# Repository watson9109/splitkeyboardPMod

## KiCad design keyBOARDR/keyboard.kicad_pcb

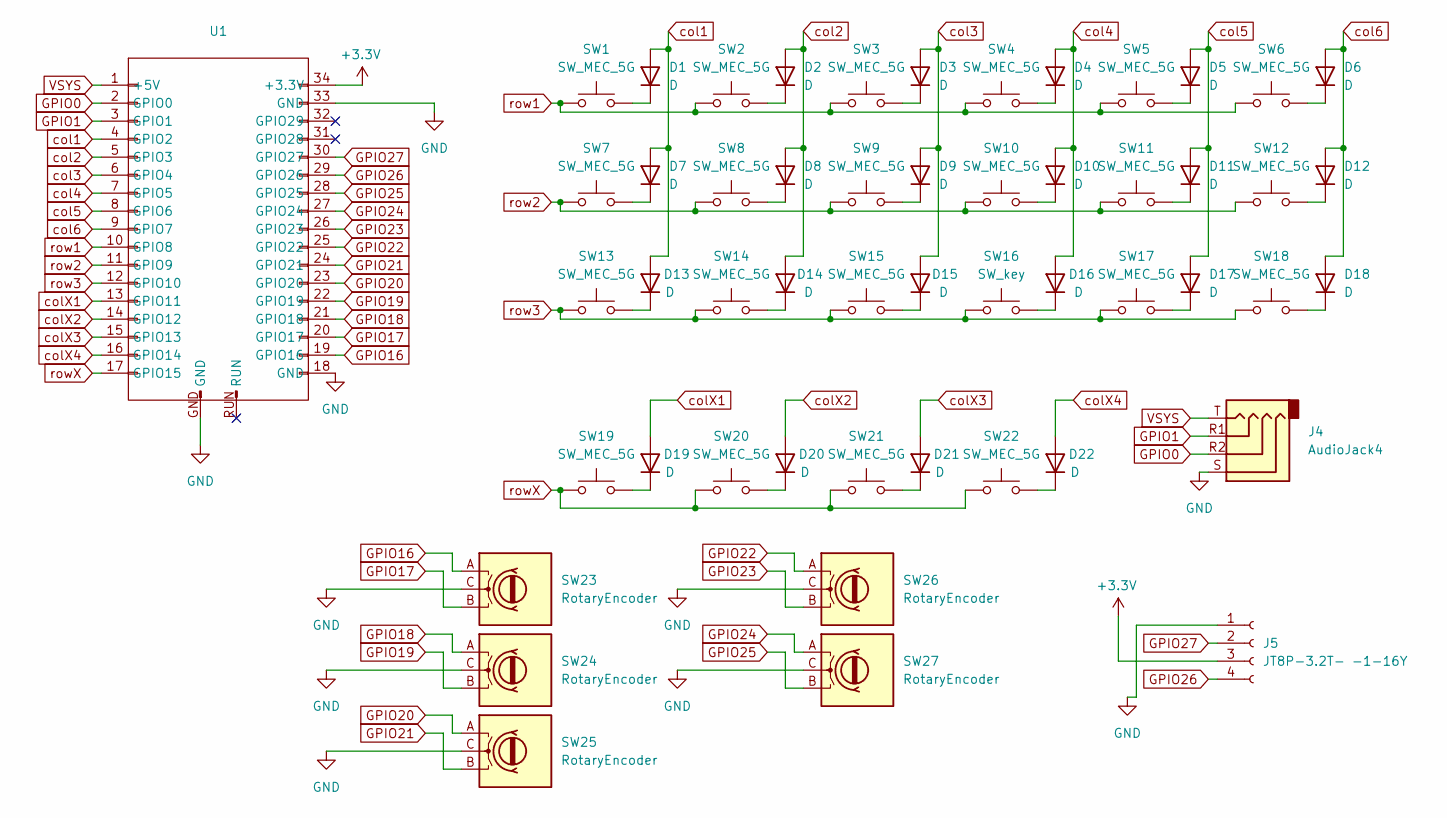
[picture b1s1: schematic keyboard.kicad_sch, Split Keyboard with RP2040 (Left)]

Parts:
D1, D2, D3, D4, D5, D6, D7, D8, D9, D10, D11, D12, D13, D14, D15, D16, D17, D18, D19, D20, D21, D22: D; D_DO-35_SOD27_P7.62mm_Horizontal
J4: AudioJack4; MJ-4PP-9
J5: JT8P-3.2T- -1-16Y
SW1, SW2, SW3, SW4, SW5, SW6, SW7, SW8, SW9, SW10, SW11, SW12, SW13, SW14, SW15, SW17, SW18, SW19, SW20, SW21, SW22: SW_MEC_5G; SW_Cherry_MX_1.00u_PCB
SW16: SW_key; SW_Cherry_MX_1.00u_PCB
SW23, SW24, SW25, SW26, SW27: RotaryEncoder; RotaryEncoder_Alps_EC12E_Vertical_H20mm_CircularMountingHol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
U1: AE-RP2040

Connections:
+3.3V: J5.3, U1.34 (+3.3V)
GND: J4.S, J5.1, SW23.C, SW24.C, SW25.C, SW26.C, SW27.C, U1.18 (GND), U1.33 (GND), U1.GND
GPIO0: J4.R2, U1.2 (GPIO0)
GPIO1: J4.R1, U1.3 (GPIO1)
GPIO16: SW23.A, U1.19 (GPIO16)
GPIO17: SW23.B, U1.20 (GPIO17)
GPIO18: SW24.A, U1.21 (GPIO18)
GPIO19: SW24.B, U1.22 (GPIO19)
GPIO20: SW25.A, U1.23 (GPIO20)
GPIO21: SW25.B, U1.24 (GPIO21)
GPIO22: SW26.A, U1.25 (GPIO22)
GPIO23: SW26.B, U1.26 (GPIO23)
GPIO24: SW27.A, U1.27 (GPIO24)
GPIO25: SW27.B, U1.28 (GPIO25)
GPIO26: J5.4, U1.29 (GPIO26)
GPIO27: J5.2, U1.30 (GPIO27)
unnamed: D1.1 (K), SW1.2 (B)
unnamed: D2.1 (K), SW2.2 (B)
unnamed: D3.1 (K), SW3.2 (B)
unnamed: D4.1 (K), SW4.2 (B)
unnamed: D5.1 (K), SW5.2 (B)
unnamed: D6.1 (K), SW6.2 (B)
unnamed: D7.1 (K), SW7.2 (B)
unnamed: D8.1 (K), SW8.2 (B)
unnamed: D9.1 (K), SW9.2 (B)
unnamed: D10.1 (K), SW10.2 (B)
unnamed: D11.1 (K), SW11.2 (B)
unnamed: D12.1 (K), SW12.2 (B)
unnamed: D13.1 (K), SW13.2 (B)
unnamed: D14.1 (K), SW14.2 (B)
unnamed: D15.1 (K), SW15.2 (B)
unnamed: D16.1 (K), SW16.2 (B)
unnamed: D17.1 (K), SW17.2 (B)
unnamed: D18.1 (K), SW18.2 (B)
unnamed: D19.1 (K), SW19.2 (B)
unnamed: D20.1 (K), SW20.2 (B)
unnamed: D21.1 (K), SW21.2 (B)
unnamed: D22.1 (K), SW22.2 (B)
VSYS: J4.T, U1.1 (+5V)
col1: D1.2 (A), D7.2 (A), D13.2 (A), U1.4 (GPIO2)
col2: D2.2 (A), D8.2 (A), D14.2 (A), U1.5 (GPIO3)
col3: D3.2 (A), D9.2 (A), D15.2 (A), U1.6 (GPIO4)
col4: D4.2 (A), D10.2 (A), D16.2 (A), U1.7 (GPIO5)
col5: D5.2 (A), D11.2 (A), D17.2 (A), U1.8 (GPIO6)
col6: D6.2 (A), D12.2 (A), D18.2 (A), U1.9 (GPIO7)
colX1: D19.2 (A), U1.13 (GPIO11)
colX2: D20.2 (A), U1.14 (GPIO12)
colX3: D21.2 (A), U1.15 (GPIO13)
colX4: D22.2 (A), U1.16 (GPIO14)
row1: SW1.1 (A), SW2.1 (A), SW3.1 (A), SW4.1 (A), SW5.1 (A), SW6.1 (A), U1.10 (GPIO8)
row2: SW7.1 (A), SW8.1 (A), SW9.1 (A), SW10.1 (A), SW11.1 (A), SW12.1 (A), U1.11 (GPIO9)
row3: SW13.1 (A), SW14.1 (A), SW15.1 (A), SW16.1 (A), SW17.1 (A), SW18.1 (A), U1.12 (GPIO10)
rowX: SW19.1 (A), SW20.1 (A), SW21.1 (A), SW22.1 (A), U1.17 (GPIO15)

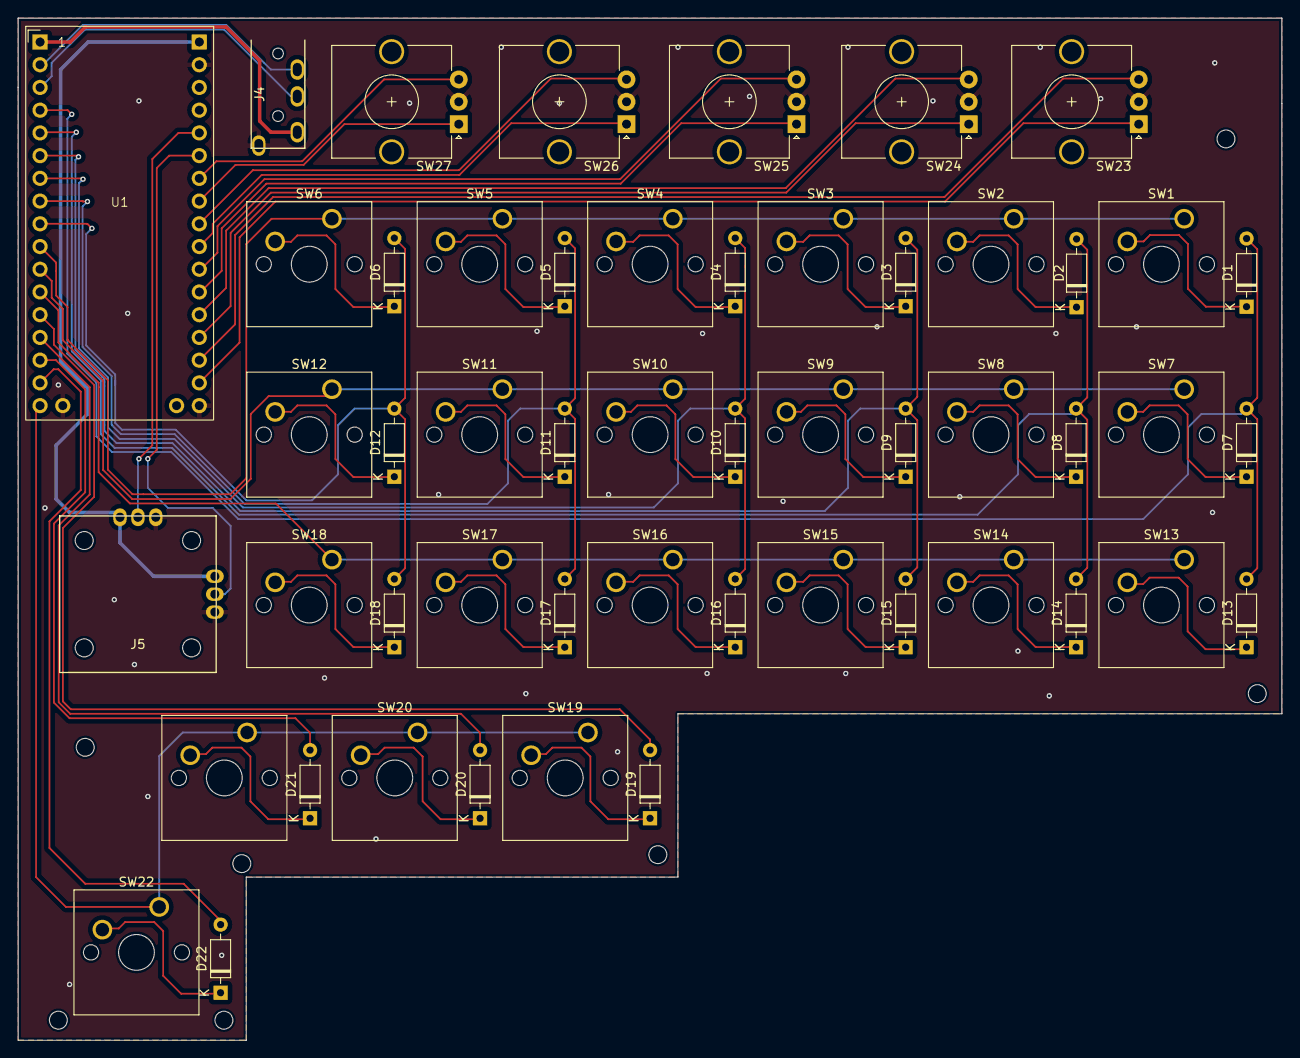
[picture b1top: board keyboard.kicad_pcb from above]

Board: 2 copper layers, 141.2 x 114.2 mm, 52 parts (0 on the bottom side), 53 nets.

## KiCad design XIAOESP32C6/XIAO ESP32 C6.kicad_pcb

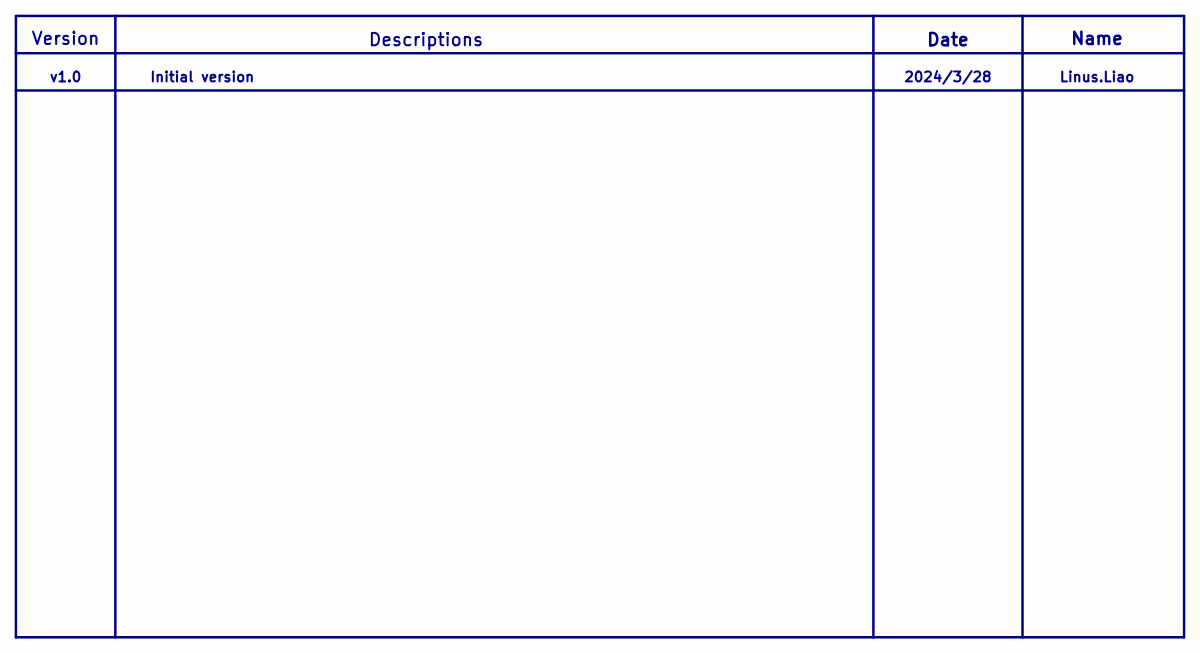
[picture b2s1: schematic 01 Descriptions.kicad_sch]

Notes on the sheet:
Date
Descriptions
Linus.Liao
2024/3/28
v1.0
Initial version
Name
Version

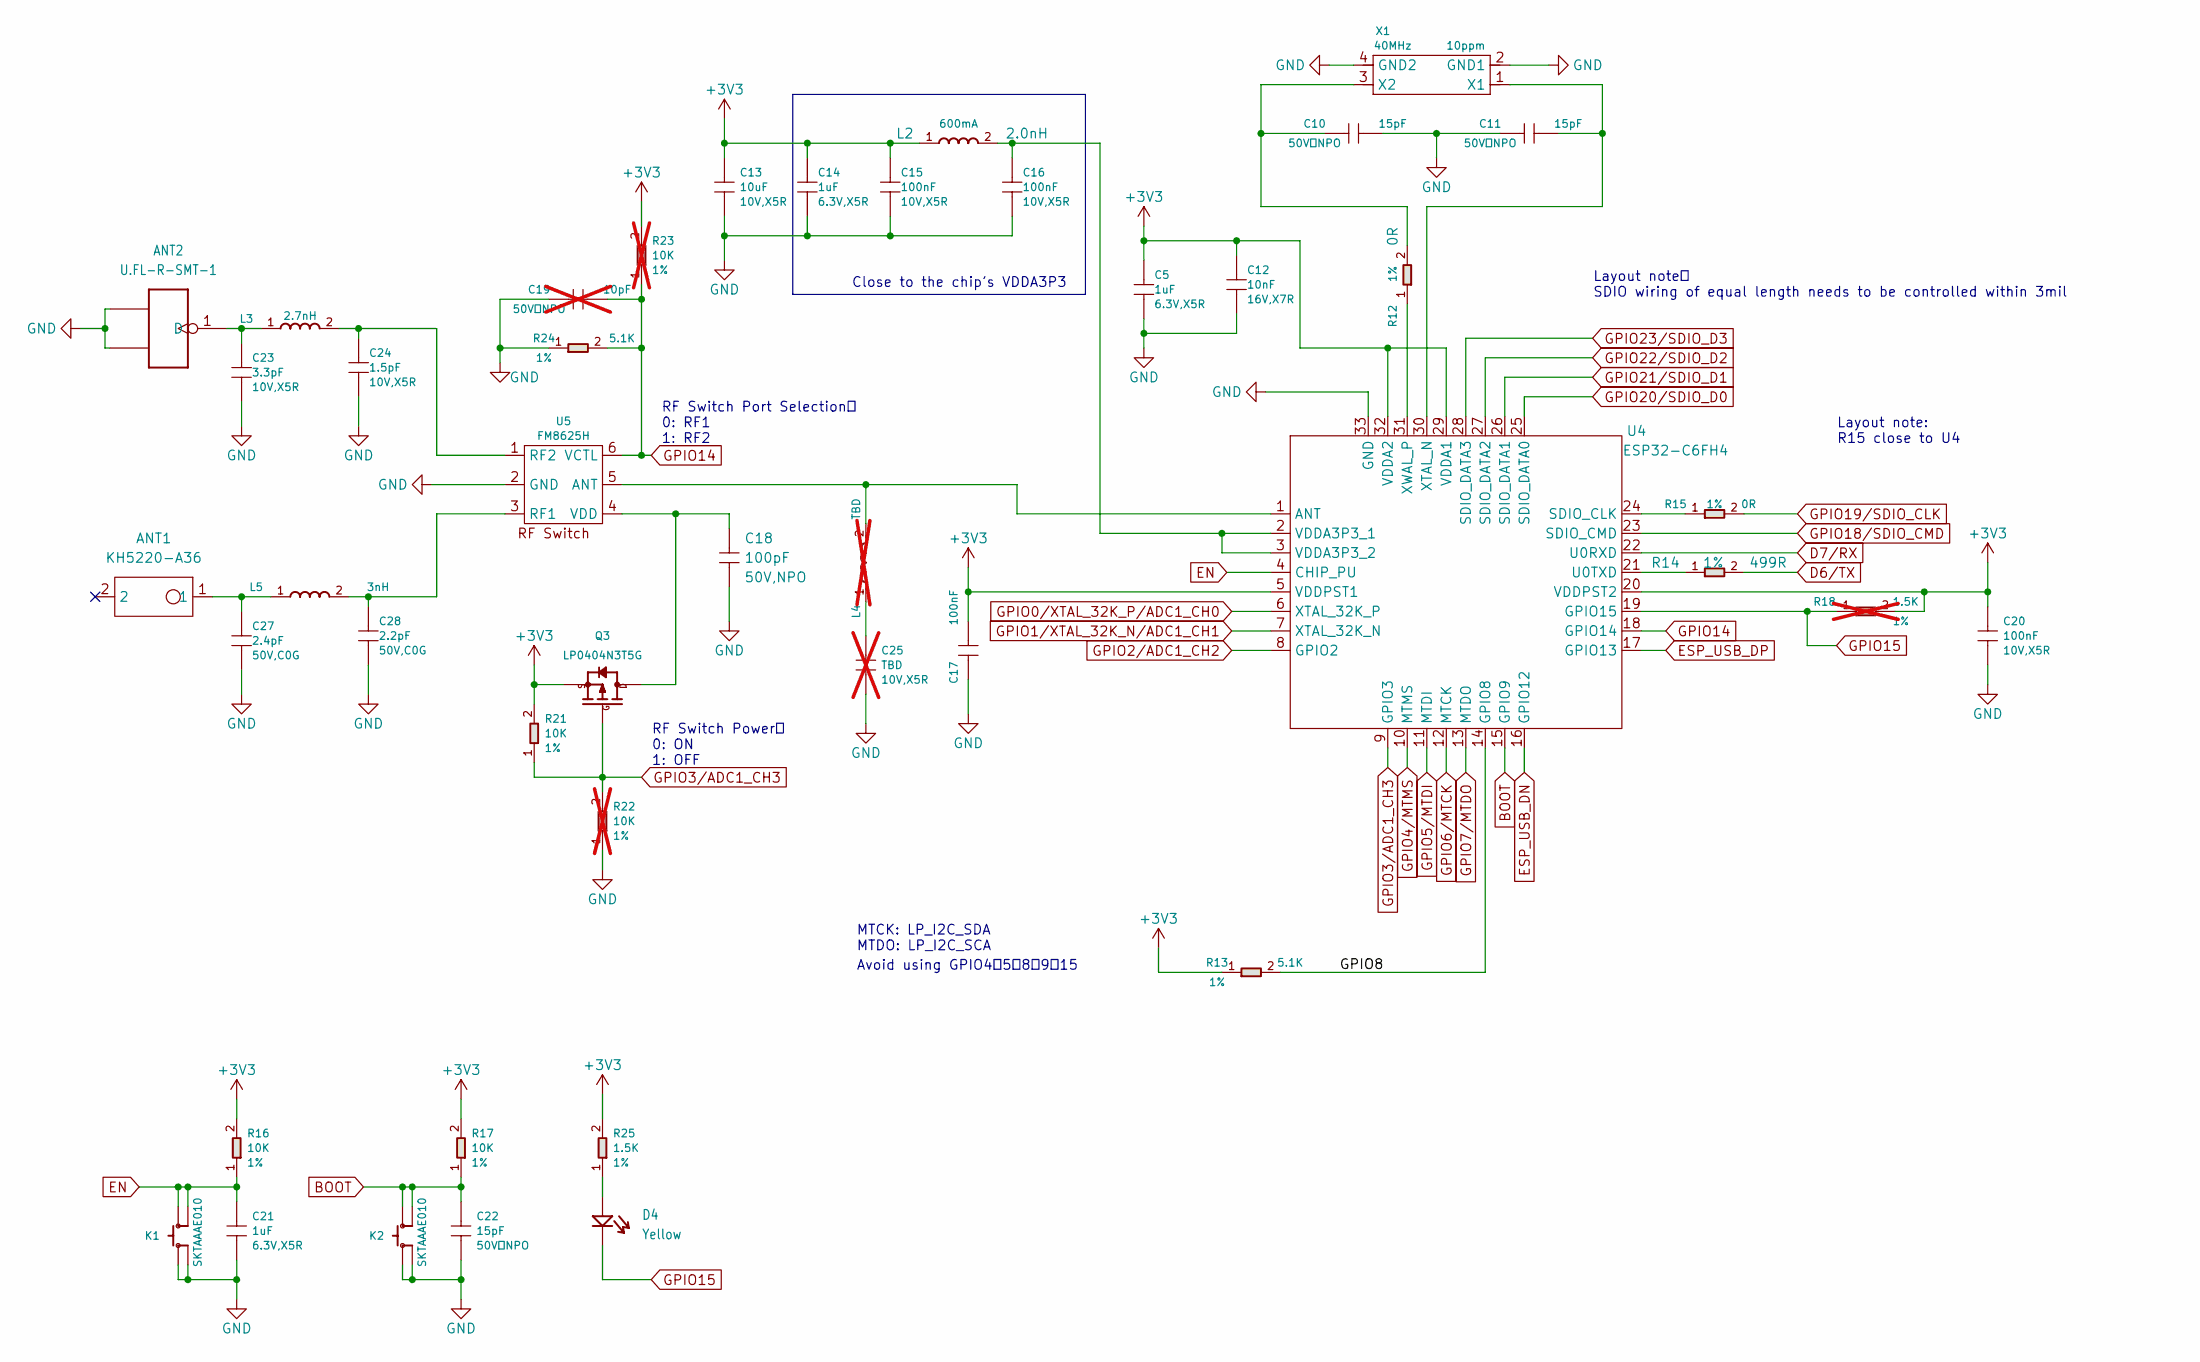
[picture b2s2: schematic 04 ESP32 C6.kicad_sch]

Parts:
ANT1: KH5220-A36; ANT2P-5.2x2x1.1MM; MPN KH5220-A36
ANT2: U.FL-R-SMT-1; U-FL3P-SMD-2.6X2.6X1.0MM; MPN U.FL-R-SMT-1
C5, C14, C21: 1uF; C0201; Voltage Rating 6.3V,X5R; MPN CC0201MRX5R5BB105
C10, C11, C22: 15pF; C0201; Voltage Rating 50V，NPO; MPN CC0201JRNPO9BN150
C12: 10nF; C0201; Voltage Rating 16V,X7R; MPN CC0201KRX7R7BB103
C13: 10uF; C0402; Voltage Rating 10V,X5R; MPN CC0402MRX5R6BB106
C15, C16, C17, C20: 100nF; C0201; Voltage Rating 10V,X5R; MPN CC0201KRX5R6BB104
C18: 100pF; C0201; Voltage Rating 50V,NPO; MPN CC0201JRNPO9BN101
C19: 10pF; C0201; Voltage Rating 50V，NPO; MPN CC0201JRNPO8BN100; not fitted
C23: 3.3pF; C0201; Voltage Rating 10V,X5R; MPN CQ0201BRNPO8BN3R3
C24: 1.5pF; C0201; Voltage Rating 10V,X5R; MPN CC0201BRNPO9BN1R5
C25: TBD; C0201; Voltage Rating 10V,X5R; Part Type Ceramic; not fitted
C27: 2.4pF; C0201; Voltage Rating 50V,C0G; MPN GRM0335C1H2R4BA01D
C28: 2.2pF; C0201; Voltage Rating 50V,C0G; MPN GRM0335C1H2R2BA01D
D4: Yellow; LED-0402; MPN 16-213/Y2C-AN2Q1B/3T
K1, K2: SKTAAAE010; SW4-SMD-2.8-2.6X1.6X0.53MM; MPN SKTAAAE010
L2: 2.0nH; L0201; Rating 600mA; MPN LQP03HQ2N0B02D
L3: 2.7nH; L0201; MPN LQP03TN2N7B02D
L4: TBD; L0201; Part Type L; not fitted
L5: 3nH; L0201; MPN LQP03TN3N0B02D
Q3: LP0404N3T5G; PMOS_1.0X0.6X0.35MM; MPN LP0404N3T5G
R12, R15: 0R; R0201; Power Rating 1%; MPN RC0201FR-070RL
R13, R24: 5.1K; R0201; Power Rating 1%; MPN RC0201FR-075K1L
R14: 499R; R0201; Power Rating 1%; MPN RC0201FR-07499RL
R16, R17, R21: 10K; R0201; Power Rating 1%; MPN RC0201FR-0710KL
R18: 1.5K; R0201; Power Rating 1%; MPN RC0201FR-071K5L; not fitted
R22, R23: 10K; R0201; Power Rating 1%; MPN RC0201FR-0710KL; not fitted
R25: 1.5K; R0201; Power Rating 1%; MPN RC0201FR-071K5L
U4: ESP32-C6FH4; QFN32-0.5-5X5MM; MPN ESP32-C6FH4
U5: FM8625H; DFN6-0.4-1.1X0.7X0.45MM; MPN FM8625H
X1: 40MHz; X4-SMD-1.6X1.2MM; Rating 10ppm; MPN CJ17-400001010B20

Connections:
+3V3: C5.1, C12.1, C13.1, C14.1, C15.1, C17.1, C20.1, L2.1, Q3.2 (S), R13.1, R16.2, R17.2, R18.2, R21.2, R23.2, R25.2, U4.5 (VDDPST1), U4.20 (VDDPST2), U4.29 (VDDA1), U4.32 (VDDA2); also elsewhere on the board
/04 ESP32 C6/GPIO8: R13.2, U4.14 (GPIO8)
BOOT: C22.1, K2.3 (B0), K2.4 (B1), R17.1, U4.15 (GPIO9); also elsewhere on the board
D6/TX: R14.2; also elsewhere on the board
D7/RX: U4.22 (U0RXD); also elsewhere on the board
EN: C21.1, K1.3 (B0), K1.4 (B1), R16.1, U4.4 (CHIP_PU); also elsewhere on the board
ESP_USB_DN: U4.16 (GPIO12); also elsewhere on the board
ESP_USB_DP: U4.17 (GPIO13); also elsewhere on the board
GND: ANT2.2 (GND1), ANT2.3 (GND2), C5.2, C10.2, C11.1, C12.2, C13.2, C14.2, C15.2, C16.2, C17.2, C18.2, C19.1, C20.2, C21.2, C22.2, C23.2, C24.2, C25.2, C27.2, C28.2, K1.1 (A0), K1.2 (A1), K2.1 (A0), K2.2 (A1), R22.1, R24.1, U4.33 (GND), U5.2 (GND), X1.2 (GND1), X1.4 (GND2); also elsewhere on the board
GPIO0/XTAL_32K_P/ADC1_CH0: U4.6 (XTAL_32K_P); also elsewhere on the board
GPIO1/XTAL_32K_N/ADC1_CH1: U4.7 (XTAL_32K_N); also elsewhere on the board
GPIO2/ADC1_CH2: U4.8 (GPIO2); also elsewhere on the board
GPIO3/ADC1_CH3: Q3.1 (G), R21.1, R22.2, U4.9 (GPIO3)
GPIO4/MTMS: U4.10 (MTMS); also elsewhere on the board
GPIO5/MTDI: U4.11 (MTDI); also elsewhere on the board
GPIO6/MTCK: U4.12 (MTCK); also elsewhere on the board
GPIO7/MTDO: U4.13 (MTDO); also elsewhere on the board
GPIO14: C19.2, R23.1, R24.2, U4.18 (GPIO14), U5.6 (VCTL)
GPIO15: D4.2 (-), R18.1, U4.19 (GPIO15)
GPIO18/SDIO_CMD: U4.23 (SDIO_CMD); also elsewhere on the board
GPIO19/SDIO_CLK: R15.2; also elsewhere on the board
GPIO20/SDIO_D0: U4.25 (SDIO_DATA0); also elsewhere on the board
GPIO21/SDIO_D1: U4.26 (SDIO_DATA1); also elsewhere on the board
GPIO22/SDIO_D2: U4.27 (SDIO_DATA2); also elsewhere on the board
GPIO23/SDIO_D3: U4.28 (SDIO_DATA3); also elsewhere on the board
unnamed: ANT1.1, C27.1, L5.1
unnamed: ANT2.1 (D), C23.1, L3.1
unnamed: C25.1, L4.1
unnamed: D4.1 (+), R25.1
unnamed: C18.1, Q3.3 (D), U5.4 (VDD)
unnamed: L4.2, U4.1 (ANT), U5.5 (ANT)
unnamed: R15.1, U4.24 (SDIO_CLK)
unnamed: R14.1, U4.21 (U0TXD)
unnamed: C16.1, L2.2, U4.2 (VDDA3P3_1), U4.3 (VDDA3P3_2)
unnamed: C11.2, U4.30 (XTAL_N), X1.1 (X1)
unnamed: R12.1, U4.31 (XWAL_P)
unnamed: C28.1, L5.2, U5.3 (RF1)
unnamed: C24.1, L3.2, U5.1 (RF2)
unnamed: C10.1, R12.2, X1.3 (X2)

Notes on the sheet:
Avoid using GPIO4、5、8、9、15
RF Switch Power： 0: ON 1: OFF
Layout note: R15 close to U4
Close to the chip's VDDA3P3
Layout note： SDIO wiring of equal length needs to be controlled within 3mil
RF Switch Port Selection： 0: RF1 1: RF2
MTCK: LP_I2C_SDA MTDO: LP_I2C_SCA

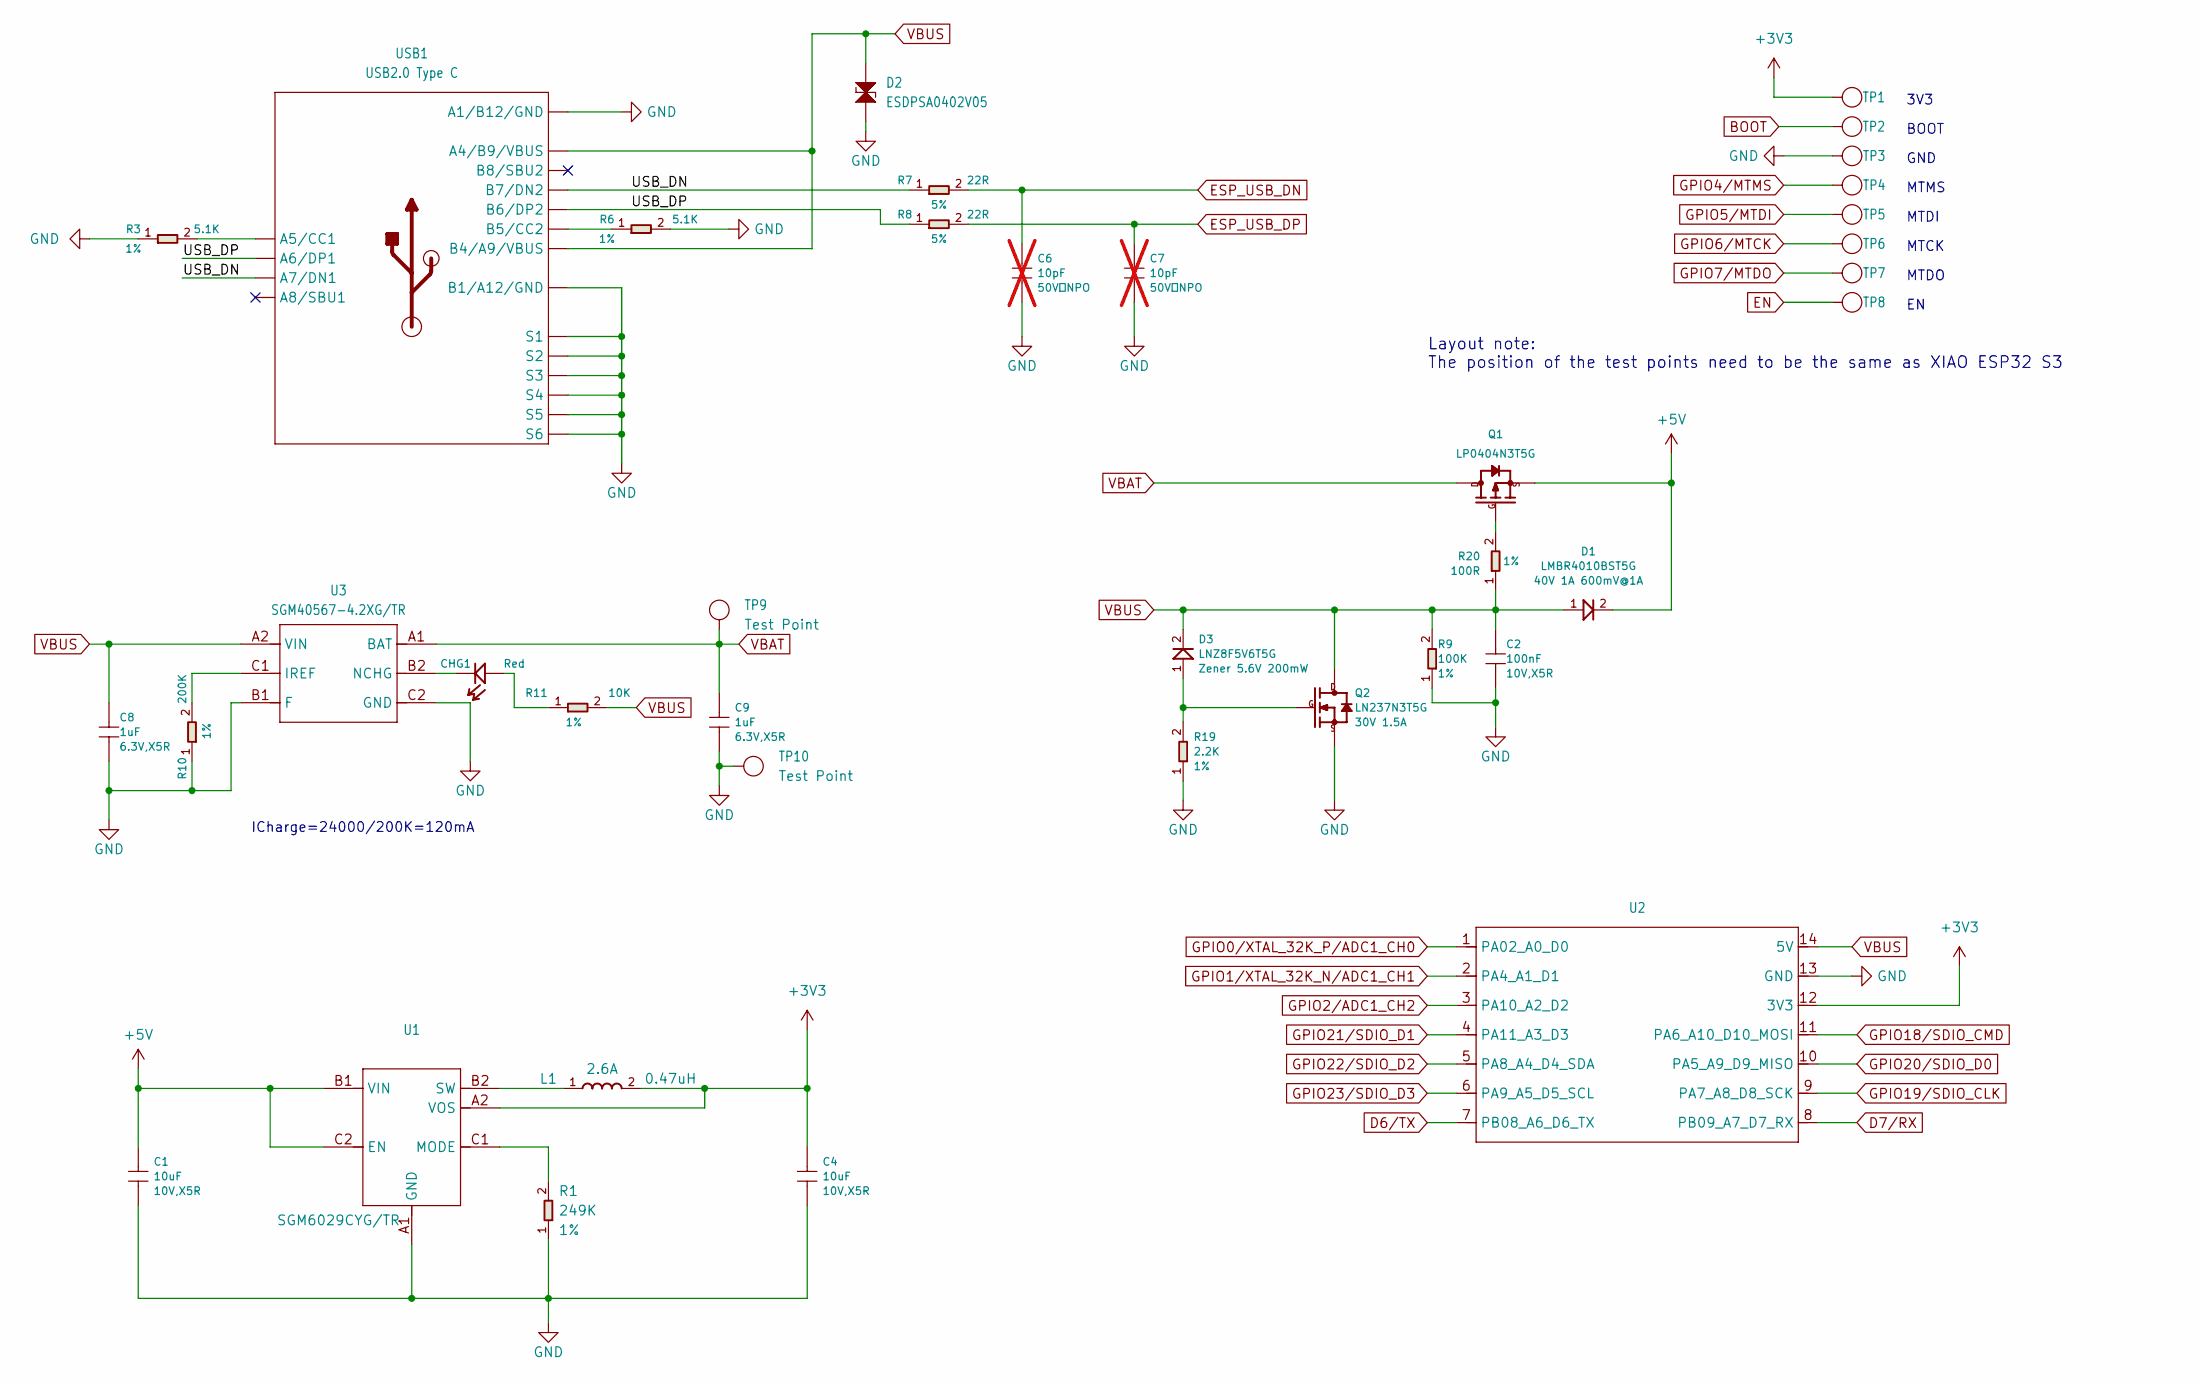
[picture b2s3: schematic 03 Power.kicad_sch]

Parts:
C1, C4: 10uF; C0402; Voltage Rating 10V,X5R; MPN CC0402MRX5R6BB106
C2: 100nF; C0201; Voltage Rating 10V,X5R; MPN CC0201KRX5R6BB104
C6, C7: 10pF; C0201; Voltage Rating 50V，NPO; MPN CC0201JRNPO8BN100; not fitted
C8, C9: 1uF; C0201; Voltage Rating 6.3V,X5R; MPN CC0201MRX5R5BB105
CHG1: Red; LED-0402; MPN BL-HUB37A-AV-TRB
D1: LMBR4010BST5G; DFN1006-2L; Rating 40V 1A 600mV@1A; MPN LMBR4010BST5G
D2: ESDPSA0402V05; ESD-0402; MPN ESDPSA0402V05
D3: LNZ8F5V6T5G; DFN1006-2L; Rating Zener 5.6V 200mW; MPN LNZ8F5V6T5G
L1: 0.47uH; L0603; Rating 2.6A; MPN TFM160808ALC-R47MTAA
Q1: LP0404N3T5G; PMOS_1.0X0.6X0.35MM; MPN LP0404N3T5G
Q2: LN237N3T5G; PMOS_1.0X0.6X0.35MM; Rating 30V 1.5A; MPN LN237N3T5G
R1: 249K; R0201; Power Rating 1%; MPN RC0201FR-07249KL
R3, R6: 5.1K; R0201; Power Rating 1%; MPN RC0201FR-075K1L
R7, R8: 22R; R0201; Power Rating 5%; MPN RC0201JR-0722RL
R9: 100K; R0201; Power Rating 1%; MPN RC0201FR-07100KL
R10: 200K; R0201; Power Rating 1%; MPN RC0201FR-07200KL
R11: 10K; R0201; Power Rating 1%; MPN RC0201FR-0710KL
R19: 2.2K; R0201; Power Rating 1%; MPN RC0201FR-072K2L
R20: 100R; R0201; Power Rating 1%; MPN RC0201FR-07100RL
TP1, TP2, TP3, TP4, TP5, TP6, TP7, TP8: Test Point; TP-D45MIL; Part Type Test Point
TP9, TP10: Test Point; TP-80X40MIL; Part Type Test Point
U1: SMD IC PMIC;DCDC Buck-ADJ-1A,Vin 1.95V to 5.5V,Vo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; BGA6-0.35-0.745X10.95X0.4MM; MPN SGM6029CYG/TR
U2: MOUDLE14P-XIAO-HALF-HOLE
U3: SGM40567-4.2XG/TR; WLCSP-0.4-0.92X1.16X0.4MM; MPN SGM40567-4.2XG/TR
USB1: USB2.0 Type C; USB2.0-TYPE-C; MPN UBF31-0171

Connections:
+3V3: C4.1, L1.2, TP1.1 (T), U1.A2 (VOS), U2.12 (3V3); also elsewhere on the board
+5V: C1.1, D1.2, Q1.2 (S), U1.B1 (VIN), U1.C2 (EN)
/03 Power/USB_DN: R7.1, USB1.A7 (A7/DN1), USB1.B7 (B7/DN2)
/03 Power/USB_DP: R8.1, USB1.A6 (A6/DP1), USB1.B6 (B6/DP2)
BOOT: TP2.1 (T); also elsewhere on the board
D6/TX: U2.7 (PB08_A6_D6_TX); also elsewhere on the board
D7/RX: U2.8 (PB09_A7_D7_RX); also elsewhere on the board
EN: TP8.1 (T); also elsewhere on the board
ESP_USB_DN: C6.1, R7.2; also elsewhere on the board
ESP_USB_DP: C7.1, R8.2; also elsewhere on the board
GND: C1.2, C2.2, C4.2, C6.2, C7.2, C8.2, C9.2, D2.1, Q2.2 (S), R1.1, R3.1, R6.2, R9.1, R10.1, R19.1, TP3.1 (T), TP10.1 (T), U1.A1 (GND), U2.13 (GND), U3.B1 (F), U3.C2 (GND), USB1.A1_B12 (A1/B12/GND), USB1.B1_A12 (B1/A12/GND), USB1.S1, USB1.S2, USB1.S3, USB1.S4, USB1.S5, USB1.S6; also elsewhere on the board
GPIO0/XTAL_32K_P/ADC1_CH0: U2.1 (PA02_A0_D0); also elsewhere on the board
GPIO1/XTAL_32K_N/ADC1_CH1: U2.2 (PA4_A1_D1); also elsewhere on the board
GPIO2/ADC1_CH2: U2.3 (PA10_A2_D2); also elsewhere on the board
GPIO4/MTMS: TP4.1 (T); also elsewhere on the board
GPIO5/MTDI: TP5.1 (T); also elsewhere on the board
GPIO6/MTCK: TP6.1 (T); also elsewhere on the board
GPIO7/MTDO: TP7.1 (T); also elsewhere on the board
GPIO18/SDIO_CMD: U2.11 (PA6_A10_D10_MOSI); also elsewhere on the board
GPIO19/SDIO_CLK: U2.9 (PA7_A8_D8_SCK); also elsewhere on the board
GPIO20/SDIO_D0: U2.10 (PA5_A9_D9_MISO); also elsewhere on the board
GPIO21/SDIO_D1: U2.4 (PA11_A3_D3); also elsewhere on the board
GPIO22/SDIO_D2: U2.5 (PA8_A4_D4_SDA); also elsewhere on the board
GPIO23/SDIO_D3: U2.6 (PA9_A5_D5_SCL); also elsewhere on the board
unnamed: CHG1.1 (+), R11.1
unnamed: CHG1.2 (-), U3.B2 (NCHG)
unnamed: Q1.1 (G), R20.2
unnamed: D3.1, Q2.1 (G), R19.2
unnamed: R1.2, U1.C1 (MODE)
unnamed: L1.1, U1.B2 (SW)
unnamed: R10.2, U3.C1 (IREF)
unnamed: R3.2, USB1.A5 (A5/CC1)
unnamed: R6.1, USB1.B5 (B5/CC2)
VBAT: C9.1, Q1.3 (D), TP9.1 (T), U3.A1 (BAT)
VBUS: C2.1, C8.1, D1.1, D2.2, D3.2, Q2.3 (D), R9.2, R11.2, R20.1, U2.14 (5V), U3.A2 (VIN), USB1.A4_B9 (A4/B9/VBUS), USB1.B4_A9 (B4/A9/VBUS)

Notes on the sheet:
MTMS
MTDI
ICharge=24000/200K=120mA
GND
MTDO
Layout note: The position of the test points need to be the same as XIAO ESP32 S3
MTCK
BOOT
3V3

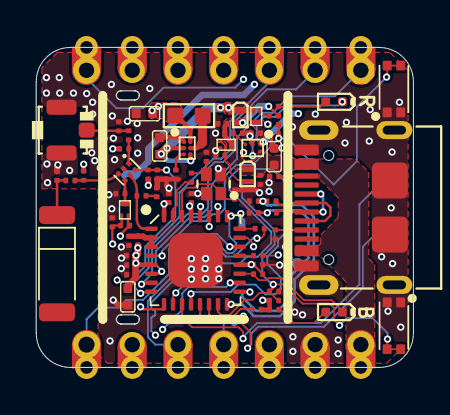
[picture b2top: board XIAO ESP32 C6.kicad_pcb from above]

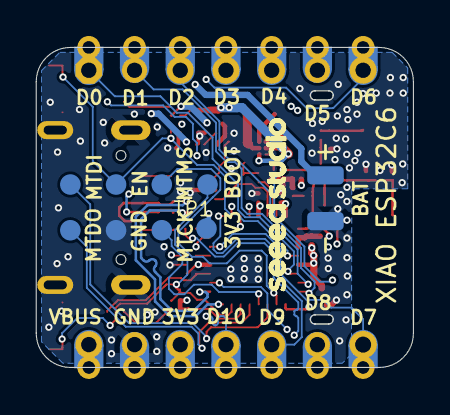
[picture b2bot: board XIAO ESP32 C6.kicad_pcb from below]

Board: 4 copper layers, 21.0 x 17.8 mm, 82 parts (10 on the bottom side), 53 nets.

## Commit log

2025-02-24 initial commit and add schematics
2025-03-25 add footprints and New design as BOARD
2025-03-25 Right part of NEW version and
2025-03-25 connect Keys and board
2025-03-25 swap lotery encoders and connect some
2025-04-03 add firmware with QMK
2025-04-03 change filename and keymaps
2025-04-07 a:wq
